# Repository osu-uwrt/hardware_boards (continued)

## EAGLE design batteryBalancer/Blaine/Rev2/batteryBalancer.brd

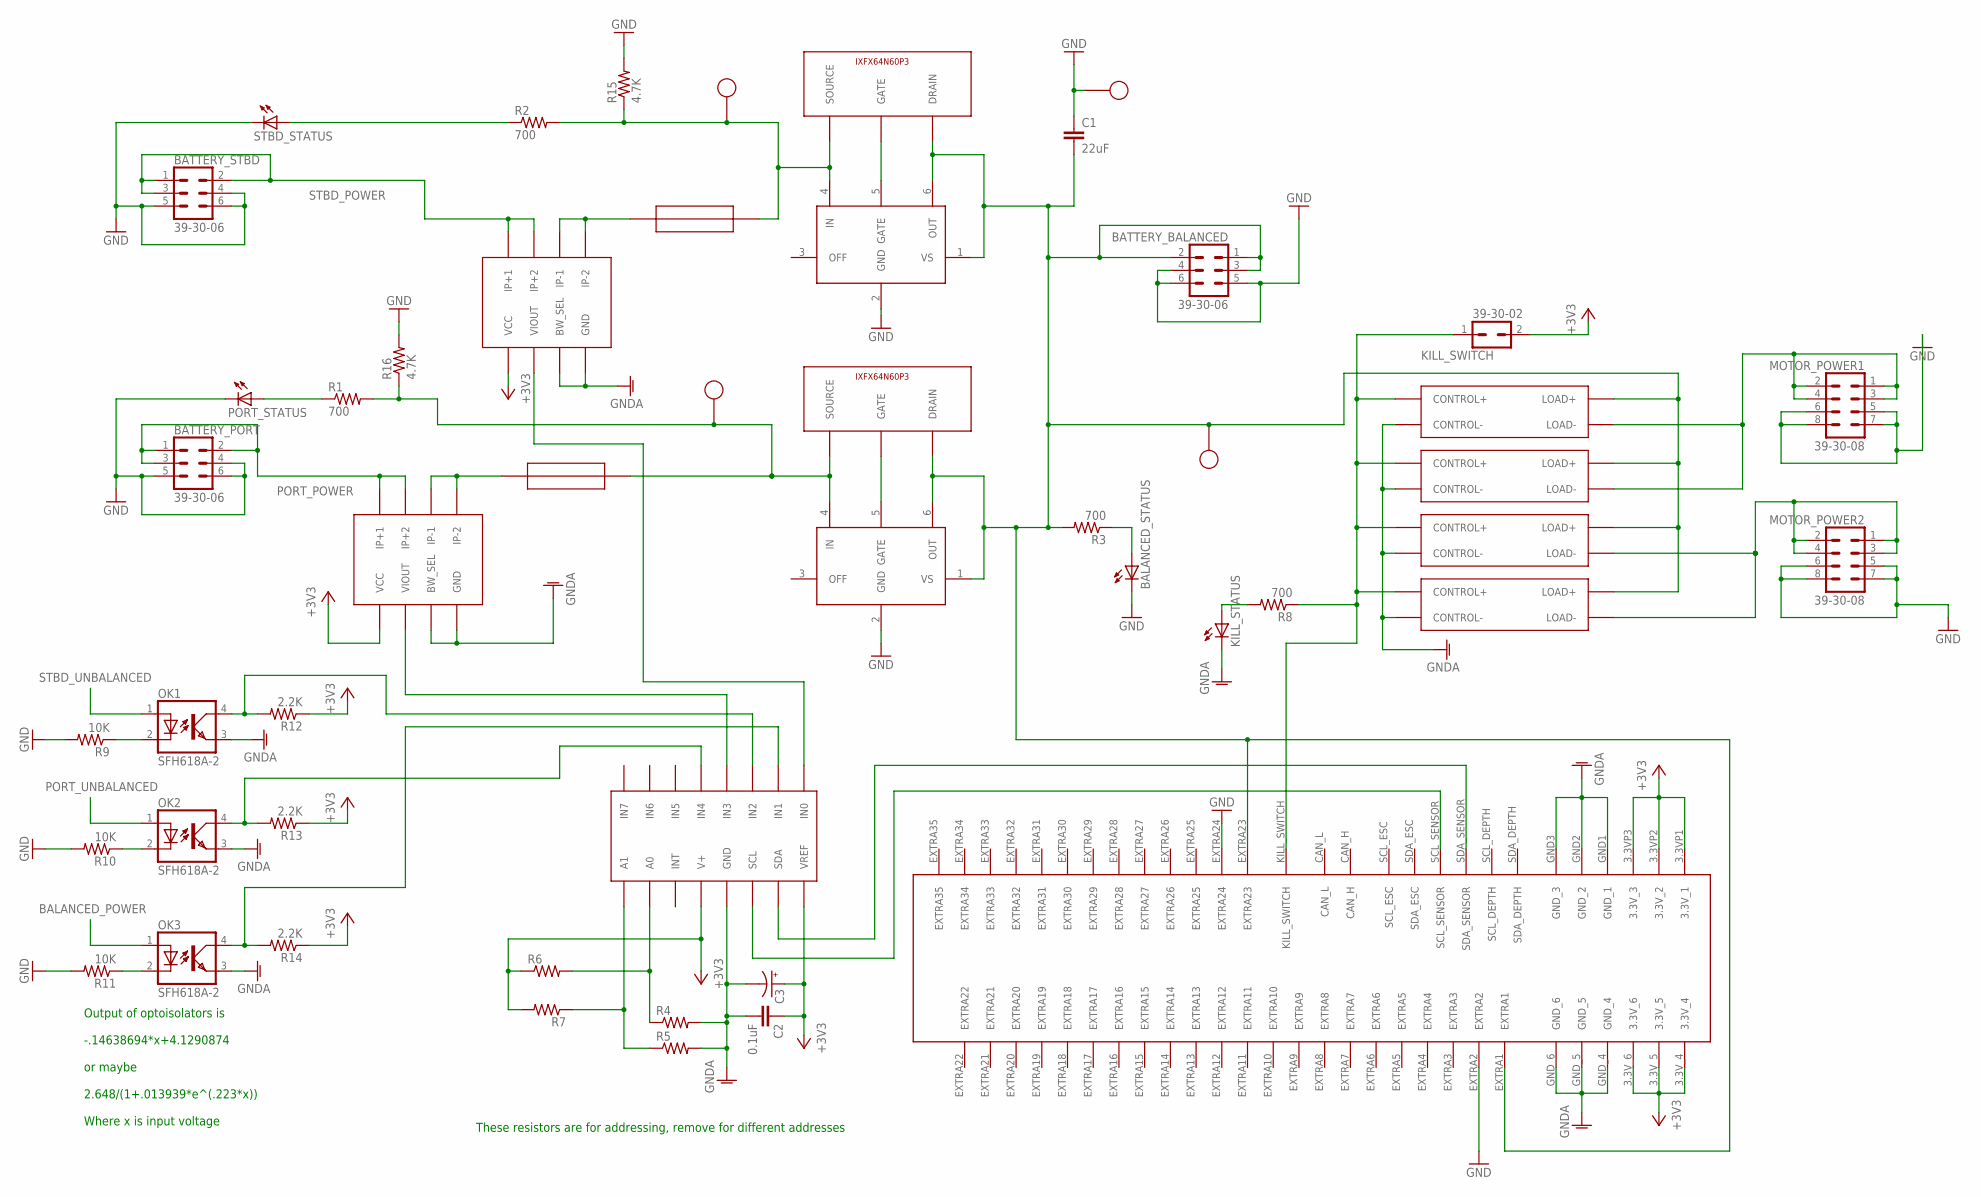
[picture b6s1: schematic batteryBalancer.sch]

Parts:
ADC: ADC128D818; TSSOP-16
BALANCED_STATUS: LTST-S270GKT
BATTERY_BALANCED: 39-30-06; 39-30-?06?
BATTERY_PORT: 39-30-06; 39-30-?06?
BATTERY_STBD: 39-30-06; 39-30-?06?
C1: 22uF; CAP-PTH-SMALL-KIT
C2: 0.1uF; CAP-PTH-SMALL-KIT
C3: CPOL-USE2-4; E2-4
EDGE_CONNECTOR: 5530843; 5530843-6-BOARDFINGERS
KILL_STATUS: LTST-S270GKT
KILL_SWITCH: 39-30-02; 39-30-?02?
MOTOR_POWER1, MOTOR_POWER2: 39-30-08; 39-30-?08?
OK1, OK2, OK3: SFH618A-2; DIP4
PORT_CS: ACS722; SOIC-8
PORT_FC: LM5050-1; SOT23-6
PORT_FET: IXFX64N60P3
PORT_FUSE: 01220083Z
PORT_STATUS: LTST-S270GKT
R1, R2, R3, R8: 700; 0207/7
R4, R5, R6, R7: R-US_0204/5; 0204/5
R9, R10, R11: 10K; 0207/7
R12, R13, R14: 2.2K; 0207/7
R15, R16: 4.7K; 0207/7
RELAY2, RELAY3, RELAY4: CMX60D20
RLAY1: CMX60D20
STBD_CS: ACS722; SOIC-8
STBD_FC: LM5050-1; SOT23-6
STBD_FET: IXFX64N60P3
STBD_FUSE: 01220083Z
STBD_STATUS: LTST-S270GKT
U$1, U$2, U$3, U$4: 5010_C

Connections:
3.3V: ADC.V+, ADC.VREF, C2.1, C3.+, EDGE_CONNECTOR.3.3VP1 (3.3V_1), EDGE_CONNECTOR.3.3VP2 (3.3V_2), EDGE_CONNECTOR.3.3VP3 (3.3V_3), EDGE_CONNECTOR.3.3V_4, EDGE_CONNECTOR.3.3V_5, EDGE_CONNECTOR.3.3V_6, KILL_SWITCH.2, PORT_CS.VCC, R6.1, R7.2, R12.1, R13.1, R14.1, STBD_CS.VCC
ADC_A0: ADC.A0, R4.1, R6.2
ADC_A1: ADC.A1, R5.1, R7.1
BALANCED_INDICATOR: BALANCED_STATUS.ANODE (A), R3.1
BALANCED_LOGIC: ADC.IN1, OK3.4 (COL), R14.2
BALANCED_OPTO_NEG: OK3.2 (C), R11.1
BALANCED_POWER: BATTERY_BALANCED.1, BATTERY_BALANCED.2, BATTERY_BALANCED.3, C1.2, EDGE_CONNECTOR.EXTRA1, EDGE_CONNECTOR.EXTRA23, OK3.1 (A), PORT_FC.1 (VS), PORT_FC.6 (OUT), PORT_FET.DRAIN, R3.2, RELAY2.LOAD+, RELAY3.LOAD+, RELAY4.LOAD+, RLAY1.LOAD+, STBD_FC.1 (VS), STBD_FC.6 (OUT), STBD_FET.DRAIN, U$3.P$1
GND: BALANCED_STATUS.CATHODE (C), BATTERY_BALANCED.4, BATTERY_BALANCED.5, BATTERY_BALANCED.6, BATTERY_PORT.4, BATTERY_PORT.5, BATTERY_PORT.6, BATTERY_STBD.4, BATTERY_STBD.5, BATTERY_STBD.6, C1.1, EDGE_CONNECTOR.EXTRA2, EDGE_CONNECTOR.EXTRA24, MOTOR_POWER1.5, MOTOR_POWER1.6, MOTOR_POWER1.7, MOTOR_POWER1.8, MOTOR_POWER2.5, MOTOR_POWER2.6, MOTOR_POWER2.7, MOTOR_POWER2.8, PORT_FC.2 (GND), PORT_STATUS.CATHODE (C), R9.2, R10.2, R11.2, R15.2, R16.2, STBD_FC.2 (GND), STBD_STATUS.CATHODE (C), U$4.P$1
KILL_SWITCH: EDGE_CONNECTOR.KILL_SWITCH, KILL_SWITCH.1, R8.1, RELAY2.CONTROL+, RELAY3.CONTROL+, RELAY4.CONTROL+, RLAY1.CONTROL+
LOGIC_GND: ADC.GND, C2.2, C3.-, EDGE_CONNECTOR.GND1 (GND_1), EDGE_CONNECTOR.GND2 (GND_2), EDGE_CONNECTOR.GND3 (GND_3), EDGE_CONNECTOR.GND_4, EDGE_CONNECTOR.GND_5, EDGE_CONNECTOR.GND_6, KILL_STATUS.CATHODE (C), OK1.3 (EMIT), OK2.3 (EMIT), OK3.3 (EMIT), PORT_CS.BW_SEL, PORT_CS.GND, R4.2, R5.2, RELAY2.CONTROL-, RELAY3.CONTROL-, RELAY4.CONTROL-, RLAY1.CONTROL-, STBD_CS.BW_SEL, STBD_CS.GND
MOTOR_POWER1: MOTOR_POWER1.1, MOTOR_POWER1.2, MOTOR_POWER1.3, MOTOR_POWER1.4, RELAY2.LOAD-, RLAY1.LOAD-
MOTOR_POWER2: MOTOR_POWER2.1, MOTOR_POWER2.2, MOTOR_POWER2.3, MOTOR_POWER2.4, RELAY3.LOAD-, RELAY4.LOAD-
unnamed: KILL_STATUS.ANODE (A), R8.2
PORT_CURRENT: ADC.IN3, PORT_CS.VIOUT
PORT_GATE: PORT_FC.5 (GATE), PORT_FET.GATE
PORT_LOGIC: ADC.IN4, OK2.4 (COL), R13.2
PORT_OPTO_NEG: OK2.2 (C), R10.1
PORT_POWER: BATTERY_PORT.1, BATTERY_PORT.2, BATTERY_PORT.3, PORT_CS.IP+1, PORT_CS.IP+2
PORT_STATUS: PORT_STATUS.ANODE (A), R1.1
PORT_UNBALANCED: OK2.1 (A), PORT_FC.4 (IN), PORT_FET.SOURCE, PORT_FUSE.P$3, PORT_FUSE.P$4, R1.2, R16.1, U$2.P$1
PORT_UNFUSED: PORT_CS.IP-1, PORT_CS.IP-2, PORT_FUSE.P$1, PORT_FUSE.P$2
SCL: ADC.SCL, EDGE_CONNECTOR.SCL_SENSOR
SDA: ADC.SDA, EDGE_CONNECTOR.SDA_SENSOR
STBD_CURRENT: ADC.IN0, STBD_CS.VIOUT
STBD_GATE: STBD_FC.5 (GATE), STBD_FET.GATE
STBD_LOGIC: ADC.IN2, OK1.4 (COL), R12.2
STBD_OPTO_NEG: OK1.2 (C), R9.1
STBD_POWER: BATTERY_STBD.1, BATTERY_STBD.2, BATTERY_STBD.3, STBD_CS.IP+1, STBD_CS.IP+2
STBD_STATUS: R2.1, STBD_STATUS.ANODE (A)
STBD_UNBALANCED: OK1.1 (A), R2.2, R15.1, STBD_FC.4 (IN), STBD_FET.SOURCE, STBD_FUSE.P$3, STBD_FUSE.P$4, U$1.P$1
STBD_UNFUSED: STBD_CS.IP-1, STBD_CS.IP-2, STBD_FUSE.P$1, STBD_FUSE.P$2

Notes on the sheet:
These resistors are for addressing, remove for different addresses
Output of optoisolators is -.14638694*x+4.1290874 or maybe 2.648/(1+.013939*e^(.223*x)) Where x is input voltage

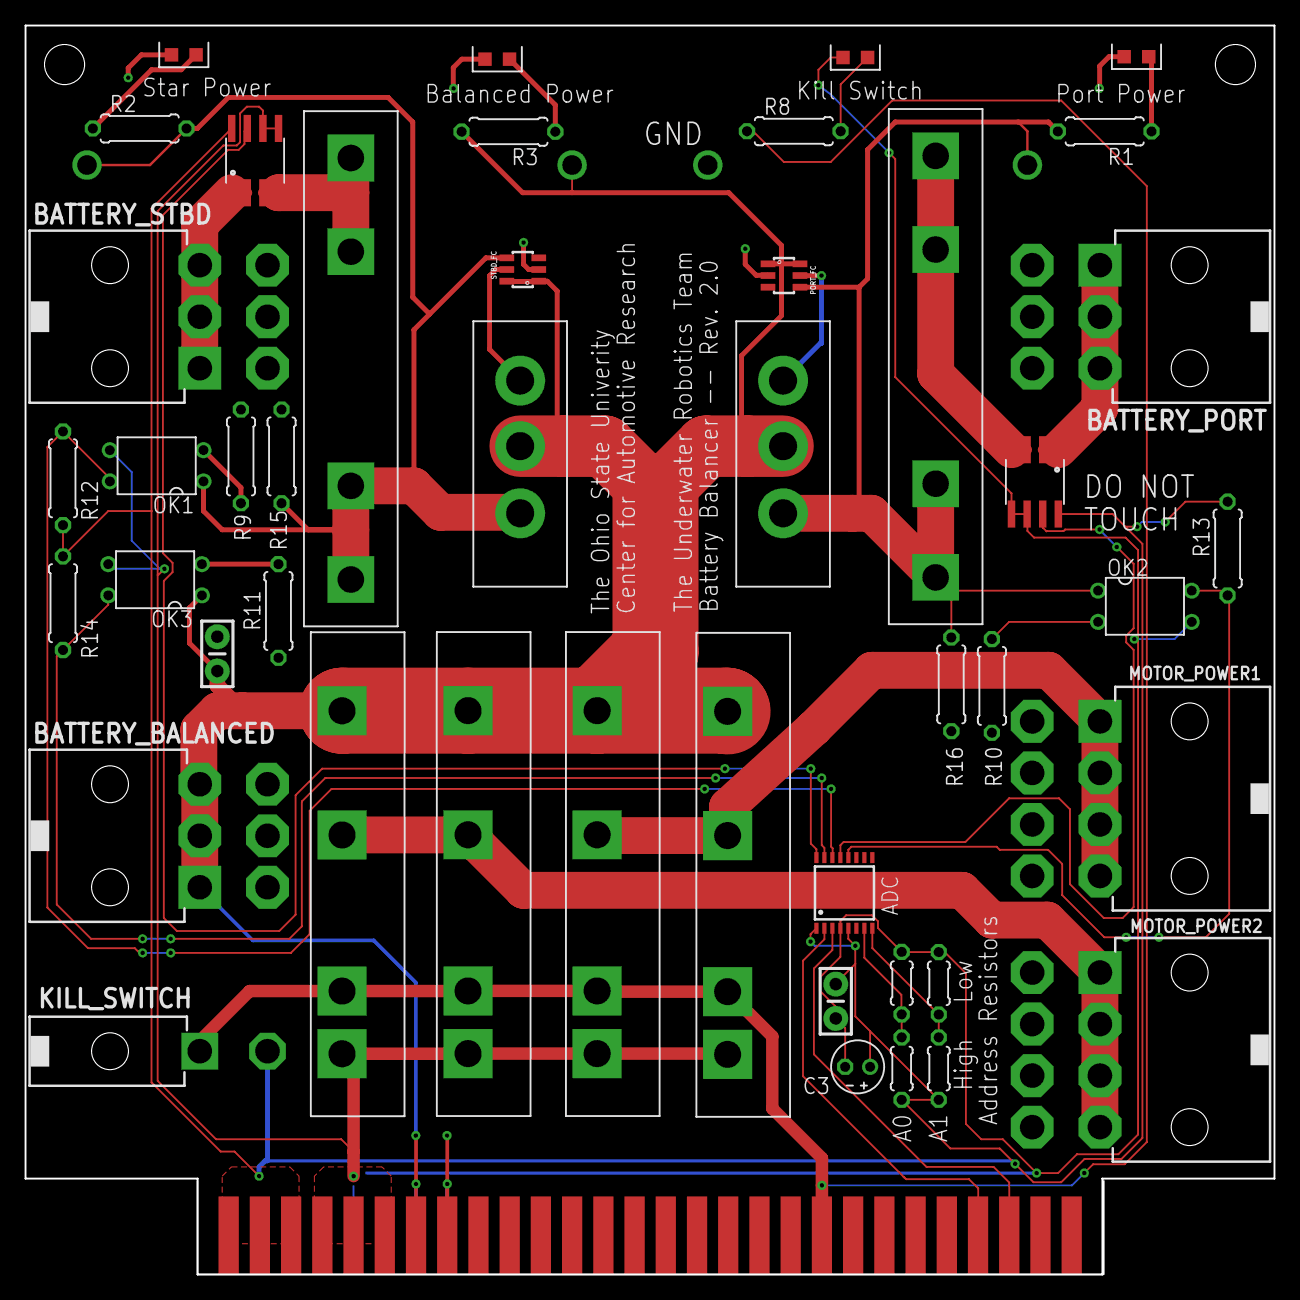
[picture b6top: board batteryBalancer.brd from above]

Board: 2 copper layers, 101.6 x 101.6 mm, 50 parts (0 on the bottom side), 31 nets.

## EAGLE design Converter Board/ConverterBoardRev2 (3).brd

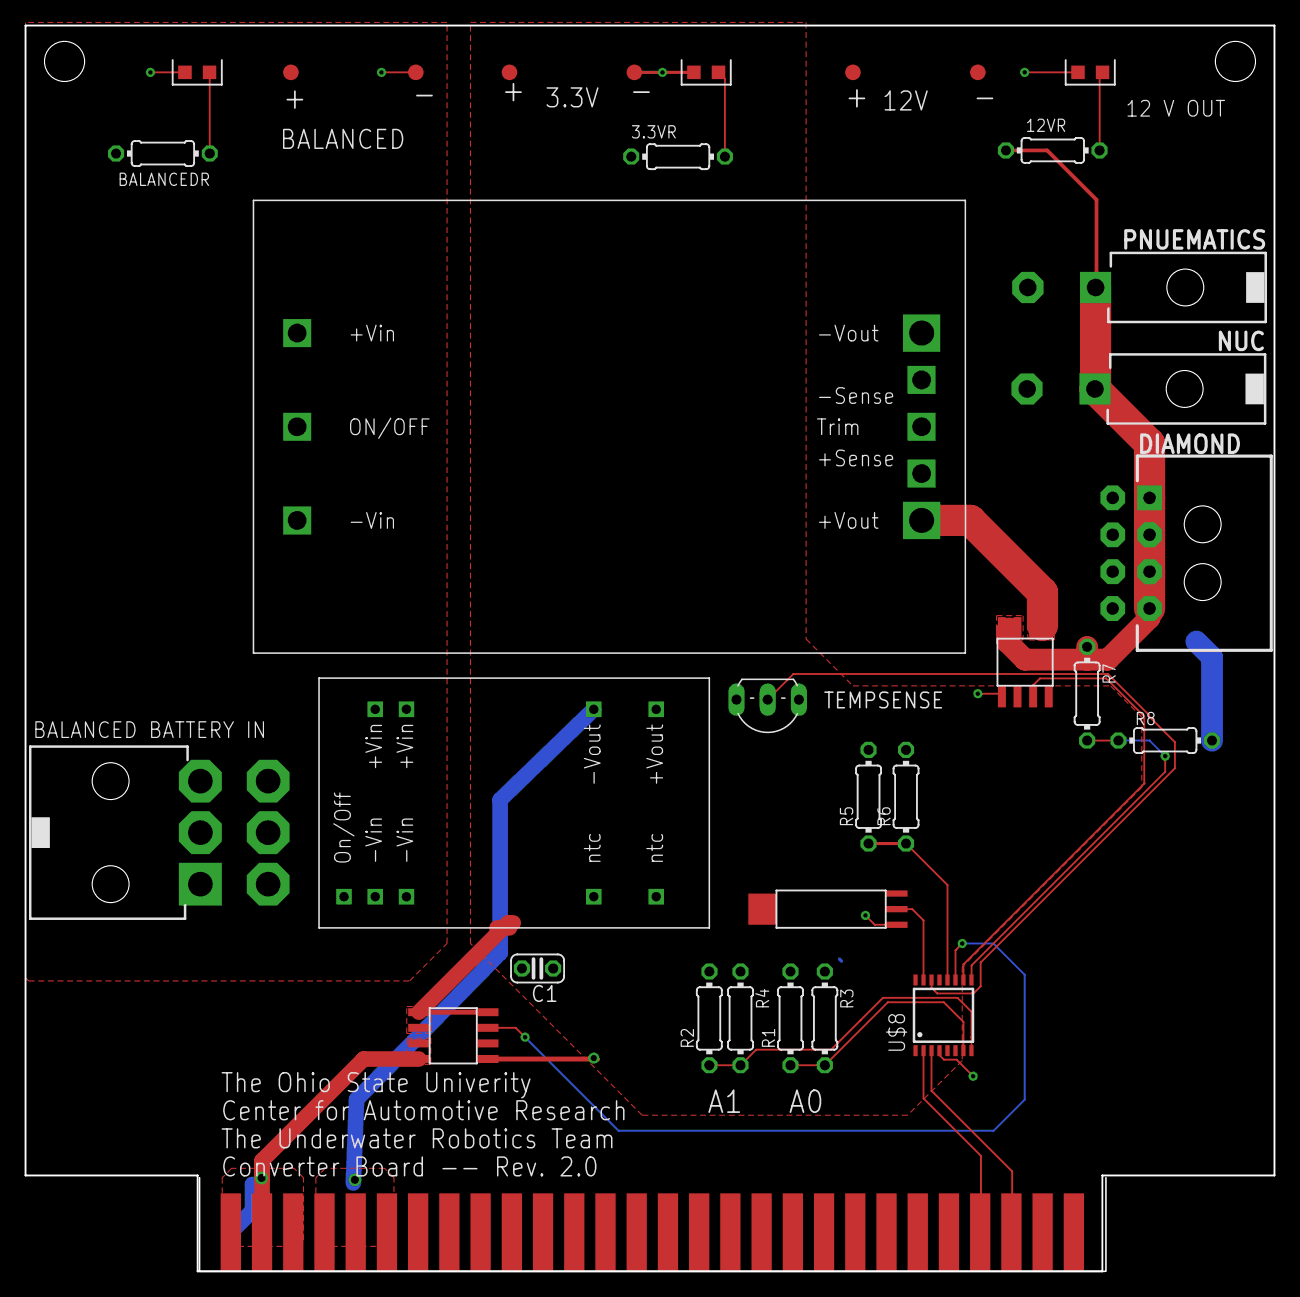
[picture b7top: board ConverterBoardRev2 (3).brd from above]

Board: 2 copper layers, 101.6 x 101.3 mm, 33 parts (0 on the bottom side), 21 nets.

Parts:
3.3V+TP, 3.3V-TP, 12V+TP, 12V-TP: PTR1B1,27; B1,27
3.3VLED, 12VLED: LTST-S270GKT
3.3VR, 12VR: 330; 0204/7
3V3CUR, 12VCUR: CURRENTSENS
BALANCED+TP: PTR1B1,27; B1,27
BALANCED-TP: PTR1B1,27; B1,27
BALANCEDLED: LTST-S270GKT
BALANCEDR: 700; 0204/7
BALANCEDRAWIN: 39-30-06?; 39-30-?06?
C1: 0.1 uF; C025-024X044
DIAMOND: 43045-08
NUC: 39-30-02?; 39-30-?02?
PNUEMATICS: 39-30-02?; 39-30-?02?
R1, R2, R3, R4, R5, R6, R7, R8: 0204/7
TEMPSENSE: 2SC458; TO92-ECB
U$1: 12VCONV
U$2: 3.3VCONV
U$3: 5530843; 5530843-6-BOARDFINGERS
U$6: HUMIDITYSENSOR
U$8: ADC128D818; TSSOP-16

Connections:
3.3IDATA: 3V3CUR.7,VIOUT, U$8.IN5
3.3V+: 3.3V+TP.TP, 3.3VR.2, 3V3CUR.1,IP+, 3V3CUR.2,IP+, 3V3CUR.8,VCC, 12VCUR.8,VCC, C1.2, R1.2, R2.2, R6.2, TEMPSENSE.E, U$2.14, U$6.+VE, U$8.V+, U$8.VREF
3.3V-: 3.3V-TP.TP, 3.3VLED.CATHODE, 3V3CUR.5,GND, 12VCUR.5,GND, C1.1, R3.1, R4.1, R5.2, TEMPSENSE.B, U$2.16, U$3.GND1, U$3.GND2, U$3.GND3, U$3.GND_4, U$3.GND_5, U$3.GND_6, U$6.-VE, U$8.GND
3.3VBKPLN: 3V3CUR.3,IP-, 3V3CUR.4,IP-, U$3.3.3VP1, U$3.3.3VP2, U$3.3.3VP3, U$3.3.3V_4, U$3.3.3V_5, U$3.3.3V_6
3.3VDATA: R5.1, R6.1, U$8.IN4
3.3VLED: 3.3VLED.ANODE, 3.3VR.1
12IDATA: 12VCUR.7,VIOUT, U$8.IN6
12VDATA: R7.2, R8.1, U$8.IN7
12VGND: 12V-TP.TP, 12VLED.CATHODE, DIAMOND.5, DIAMOND.6, DIAMOND.7, DIAMOND.8, NUC.2, PNUEMATICS.2, R8.2, U$1.4,-VOUT
12VLED: 12VLED.ANODE, 12VR.2
12VMON: 12VCUR.3,IP-, 12VCUR.4,IP-, 12VR.1, DIAMOND.1, DIAMOND.2, DIAMOND.3, DIAMOND.4, NUC.1, PNUEMATICS.1, R7.1
12VUNMON: 12VCUR.1,IP+, 12VCUR.2,IP+, U$1.8,+VOUT
A0: R1.1, R3.2, U$8.A0
A1: R2.1, R4.2, U$8.A1
BALANCED+: BALANCED+TP.TP, BALANCEDR.2, BALANCEDRAWIN.4, BALANCEDRAWIN.5, BALANCEDRAWIN.6, U$1.1,+VIN, U$1.2,ON/OFF, U$2.22, U$2.23
BALANCED-: BALANCED-TP.TP, BALANCEDLED.CATHODE, BALANCEDRAWIN.1, BALANCEDRAWIN.2, BALANCEDRAWIN.3, U$1.3,-VIN, U$2.1, U$2.2, U$2.3
BALANCEDLED: BALANCEDLED.ANODE, BALANCEDR.1
HUMIDITYDATA: U$6.OUT, U$8.IN1
SCL: U$3.SCL_SENSOR, U$8.SCL
SDA: U$3.SDA_SENSOR, U$8.SDA
TEMPDATA: TEMPSENSE.C, U$8.IN2

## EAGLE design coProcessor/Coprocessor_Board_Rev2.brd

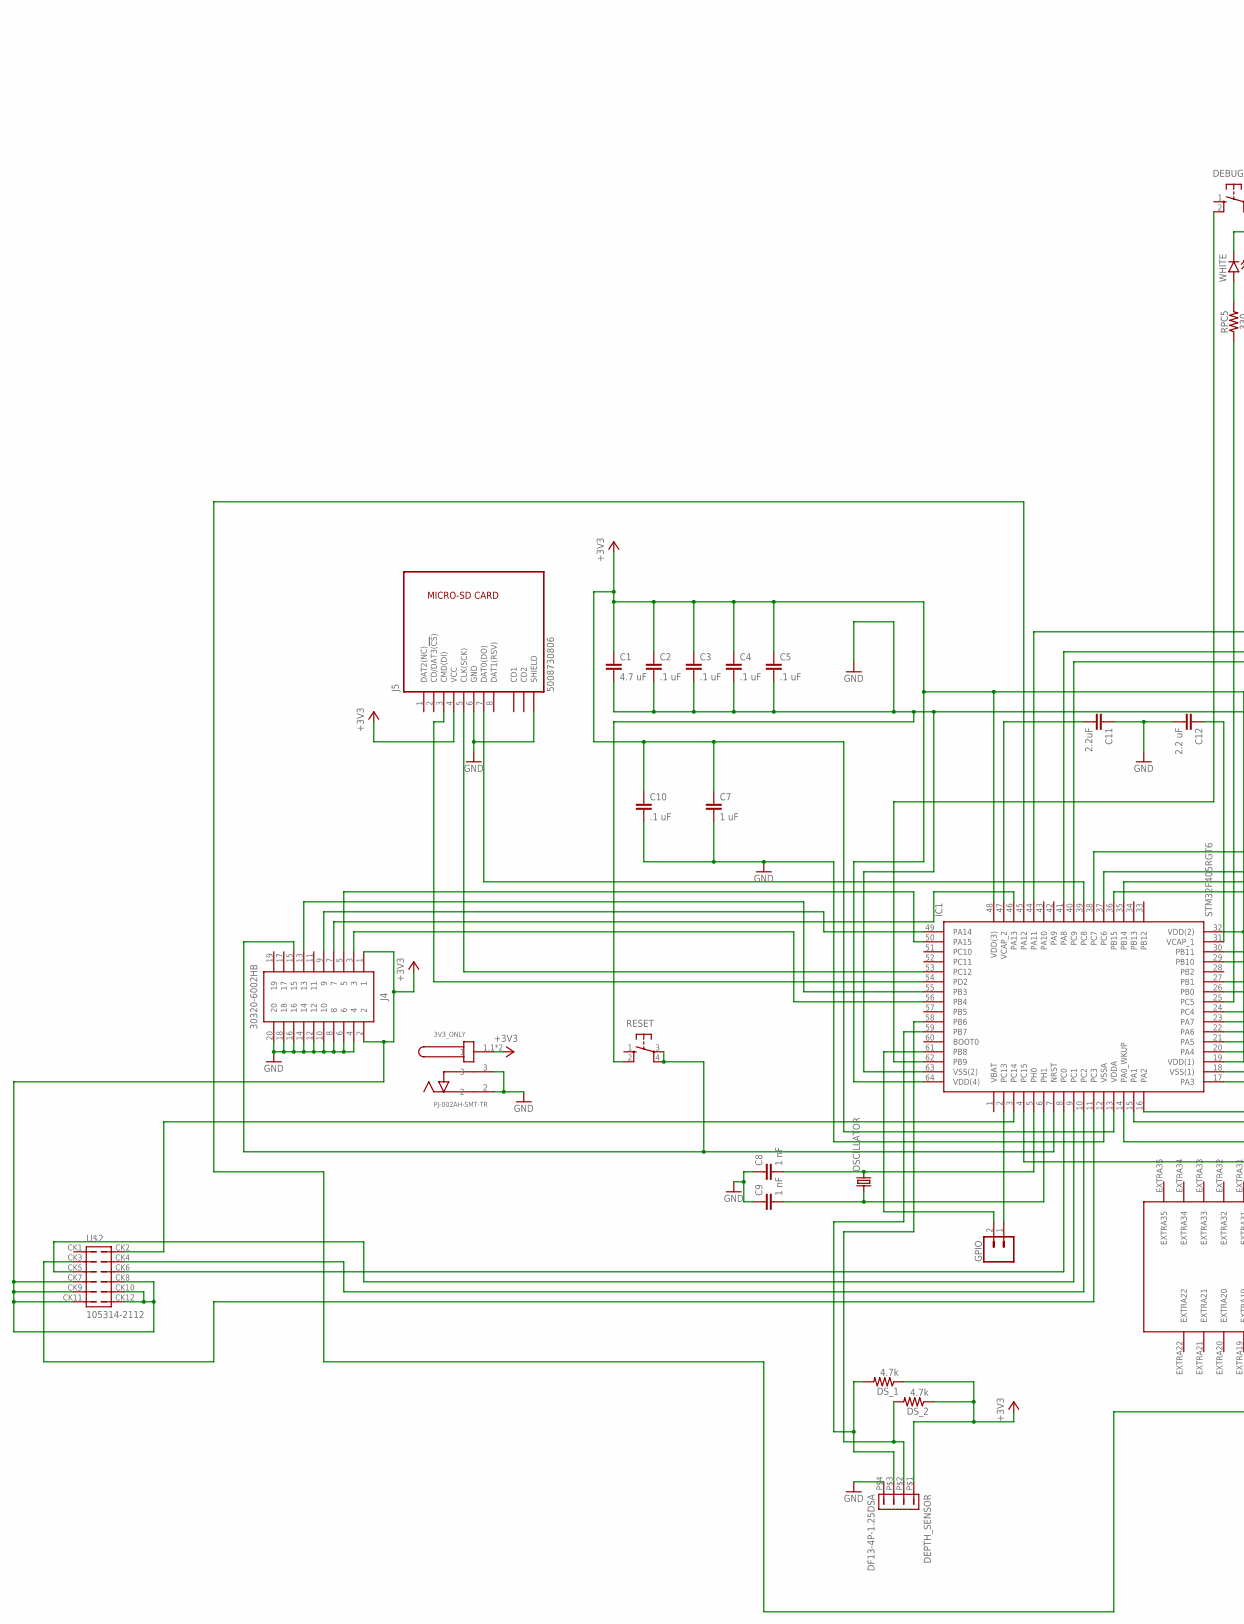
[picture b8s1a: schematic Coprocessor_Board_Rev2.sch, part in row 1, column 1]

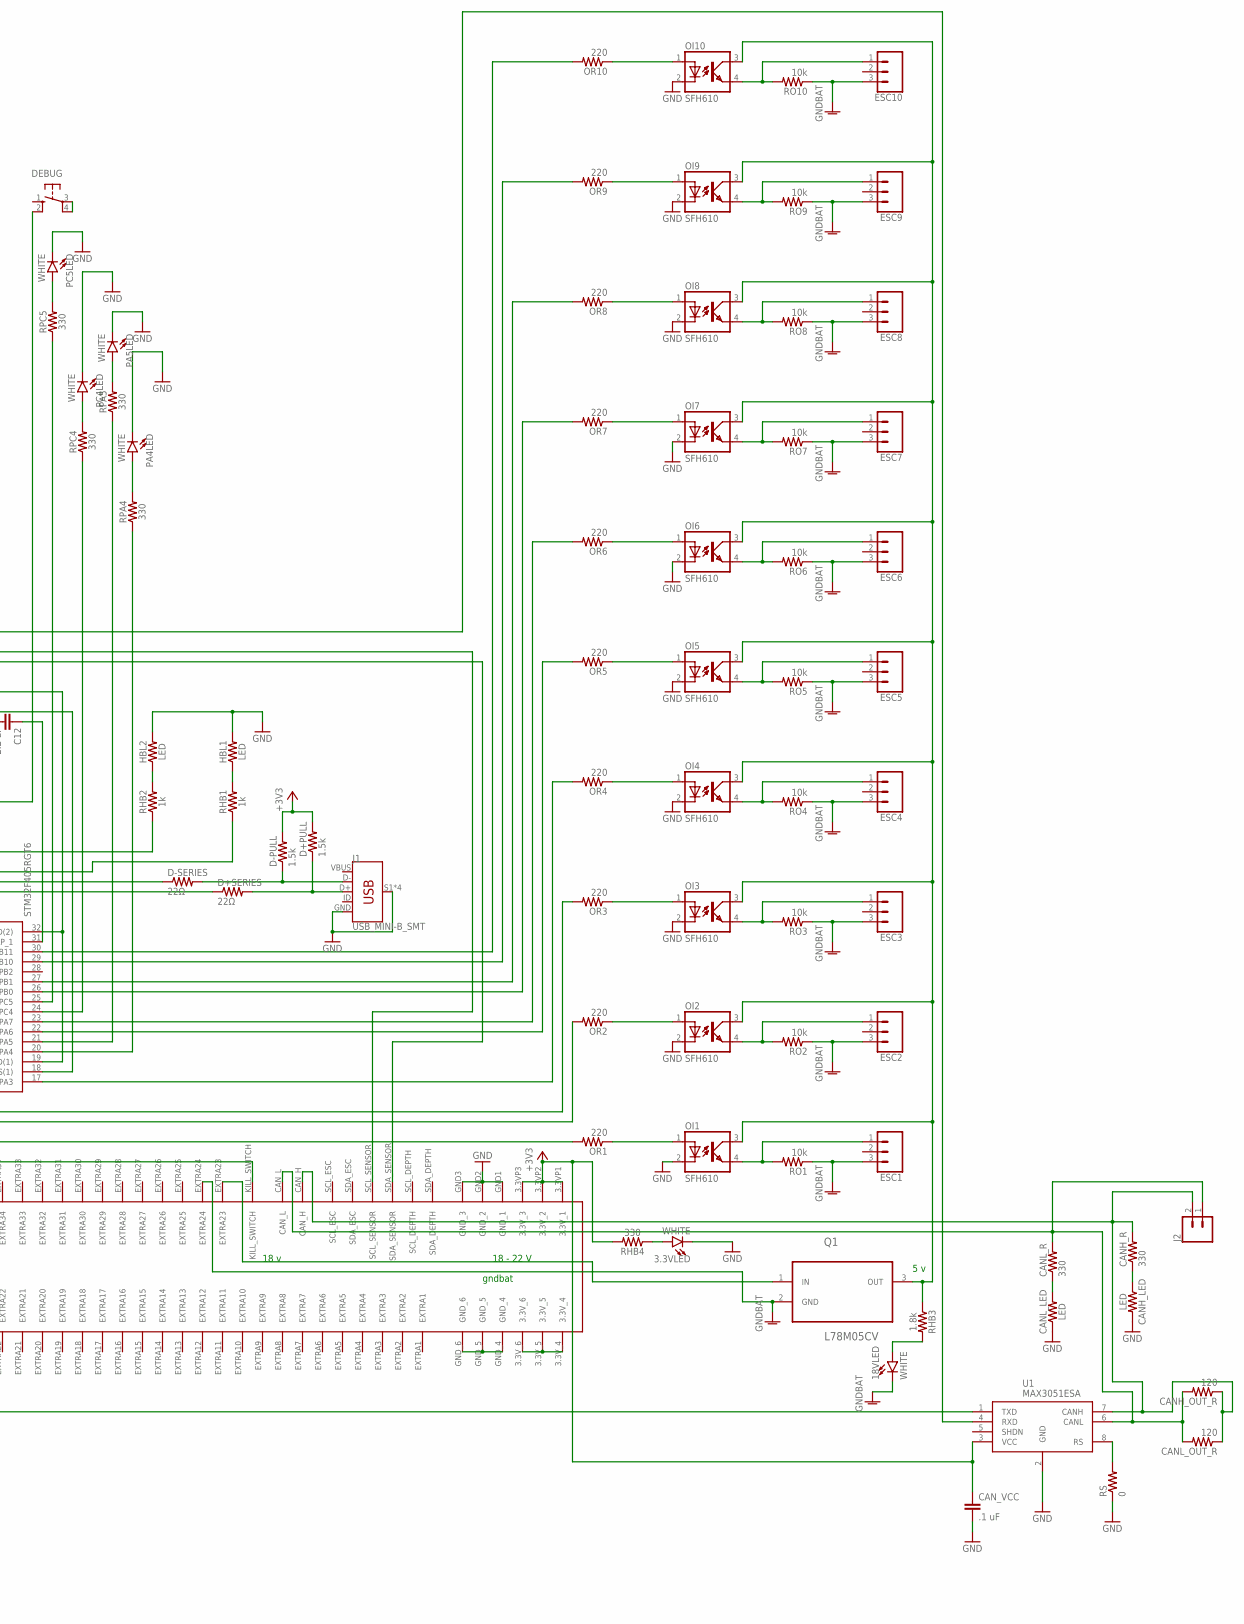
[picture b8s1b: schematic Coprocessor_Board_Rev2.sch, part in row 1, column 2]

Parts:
3.3VLED, 18VLED: WHITE; LED-1206
3V3_ONLY: PJ-002AH-SMT-TR; CUI_PJ-002AH-SMT-TR
C1: 4.7 uF; 0603
C2, C3, C4, C5, C10: .1 uF; 0603
C7: 1 uF; 0603
C8, C9: 1 nF; CAP-PTH-2.54
C11: 2.2uF; 0603
C12: 2.2 uF; 0603
CANH_LED: LED; AXIAL-0.1
CANH_OUT_R: 120; 0204/7
CANH_R: 330; 0204/7
CANL_LED: LED; AXIAL-0.1
CANL_OUT_R: 120; 0204/7
CANL_R: 330; 0204/7
CAN_VCC: .1 uF; CAP-PTH-2.54
D+PULL: 1.5k; 0204/7
D+SERIES: 22Ω; 0204/7
D-PULL: 1.5k; 0204/7
D-SERIES: 22Ω; 0204/7
DEBUG: 10-XX; B3F-10XX
DEPTH_SENSOR: DF13-4P-1.25DSA
DS_1, DS_2: 4.7k; 0204/7
ESC1, ESC2, ESC3, ESC4, ESC5, ESC6, ESC7, ESC8, ESC9, ESC10: CONN_03; 1X03
GPIO: CONN_02; 1X02
HBL1, HBL2: LED; AXIAL-0.1
IC1: STM32F405RGT6; QFP50P1200X1200X160-64N
J1: USB_MINI-B_SMT; USB-MINIB
J2: CONN_02; 1X02
J4: 30320-6002HB; SHDR20W81P254_2X10_3300X840X93
J5: 5008730806
OI1, OI2, OI3, OI4, OI5, OI6, OI7, OI8, OI9, OI10: SFH610; DIL04
OR1, OR2, OR3, OR4, OR5, OR6, OR7, OR8, OR9, OR10: 220; 0204/7
OSCILLATOR: CRYSTALHC49S; HC49/S
PA4LED, PA5LED: WHITE; LED-1206
PC4LED, PC5LED: WHITE; LED-1206
Q1: L78M05CV; TO254P450X1020X1935-3P
RESET: 10-XX; B3F-10XX
RHB1, RHB2: 1k; AXIAL-0.3
RHB3: 1.8k; AXIAL-0.3
RHB4: 330; AXIAL-0.3
RO1, RO2, RO3, RO4, RO5, RO6, RO7, RO8, RO9, RO10: 10k; 0204/7
RPA4, RPA5: 330; AXIAL-0.3
RPC4, RPC5: 330; AXIAL-0.3
RS: 0; 0204/7
U1: MAX3051ESA; 8-SOICN
U$1: 5530843; 5530843-6-BOARDFINGERS
U$2: 105314-2112

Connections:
3.3V: 3V3_ONLY.1.1 (1), 3V3_ONLY.1.2 (1), C1.1, C2.1, C3.1, C4.1, C5.1, C7.1, C10.1, CAN_VCC.1, D+PULL.2, D-PULL.2, DEPTH_SENSOR.P$1 (1), DS_1.1, DS_2.1, IC1.13 (VDDA), IC1.19 (VDD(1)), IC1.32 (VDD(2)), IC1.48 (VDD(3)), IC1.64 (VDD(4)), J4.1, J4.2, J5.4 (VCC), RHB4.P$2 (2), U1.3 (VCC), U$1.3.3VP1 (3.3V_1), U$1.3.3VP2 (3.3V_2), U$1.3.3VP3 (3.3V_3), U$1.3.3V_4, U$1.3.3V_5, U$1.3.3V_6, U$2.CK7, U$2.CK8, U$2.CK9, U$2.CK10, U$2.CK11, U$2.CK12
5V: OI1.3 (COL), OI2.3 (COL), OI3.3 (COL), OI4.3 (COL), OI5.3 (COL), OI6.3 (COL), OI7.3 (COL), OI8.3 (COL), OI9.3 (COL), OI10.3 (COL), Q1.3 (OUT), RHB3.P$1 (1)
18V: Q1.1 (IN), U$1.EXTRA23
CAN1_RXD: IC1.44 (PA11), U1.4 (RXD)
CAN1_TXD: IC1.45 (PA12), U1.1 (TXD)
CANH: CANH_OUT_R.1, CANH_R.2, CANL_OUT_R.1, J2.2, U1.7 (CANH), U$1.CAN_H
CANL: CANH_OUT_R.2, CANL_OUT_R.2, CANL_R.2, J2.1, U1.6 (CANL), U$1.CAN_L
D+CON: D+PULL.1, D+SERIES.2, J1.D+
D-CON: D-PULL.1, D-SERIES.2, J1.D-
DEPTHSCL: DEPTH_SENSOR.P$2 (2), DS_2.2, IC1.58 (PB6)
DEPTHSDA: DEPTH_SENSOR.P$3 (3), DS_1.2, IC1.59 (PB7)
GNDBAT: 18VLED.C, ESC1.3, ESC2.3, ESC3.3, ESC4.3, ESC5.3, ESC6.3, ESC7.3, ESC8.3, ESC9.3, ESC10.3, Q1.2 (GND), RO1.1, RO2.1, RO3.1, RO4.1, RO5.1, RO6.1, RO7.1, RO8.1, RO9.1, RO10.1, U$1.EXTRA24
HEARTBEAT_1: IC1.37 (PC6), RHB1.P$1 (1)
HEARTBEAT_2: IC1.38 (PC7), RHB2.P$1 (1)
HEARTBEAT_3: IC1.20 (PA4), RPA4.P$1 (1)
HEARTBEAT_4: IC1.21 (PA5), RPA5.P$1 (1)
HEAVE_PORT_AFT: IC1.27 (PB1), OR8.2
HEAVE_PORT_FWD: IC1.26 (PB0), OR7.2
HEAVE_STBD_AFT: IC1.23 (PA7), OR6.2
HEAVE_STBD_FWD: IC1.22 (PA6), OR5.2
JTAG15: IC1.7 (NRST), J4.15, RESET.3, RESET.4 (P1)
KILLSWITCH: IC1.4 (PC15), U$1.KILL_SWITCH
MISSION_START: IC1.8 (PC0), U$2.CK6
unnamed: HBL1.P$1 (1), RHB1.P$2 (2)
unnamed: RS.2, U1.8 (RS)
unnamed: 18VLED.A, RHB3.P$2 (2)
unnamed: 3.3VLED.A, RHB4.P$1 (1)
unnamed: CANH_LED.P$1 (1), CANH_R.1
unnamed: CANL_LED.P$2 (2), CANL_R.1
unnamed: PA4LED.A, RPA4.P$2 (2)
unnamed: PA5LED.A, RPA5.P$2 (2)
unnamed: PC4LED.A, RPC4.P$2 (2)
unnamed: PC5LED.A, RPC5.P$2 (2)
unnamed: HBL2.P$1 (1), RHB2.P$2 (2)
PB8: GPIO.2, IC1.61 (PB8)
PB9: DEBUG.2 (S1), IC1.62 (PB9)
PC4: IC1.24 (PC4), RPC4.P$1 (1)
PC5: IC1.25 (PC5), RPC5.P$1 (1)
PC13: GPIO.1, IC1.2 (PC13)
PWM1: OI1.1 (A), OR1.1
PWM2: OI2.1 (A), OR2.1
PWM3: OI3.1 (A), OR3.1
PWM4: OI4.1 (A), OR4.1
PWM5: OI5.1 (A), OR5.1
PWM5V1: ESC1.1, OI1.4 (EMIT), RO1.2
PWM5V2: ESC2.1, OI2.4 (EMIT), RO2.2
PWM5V3: ESC3.1, OI3.4 (EMIT), RO3.2
PWM5V4: ESC4.1, OI4.4 (EMIT), RO4.2
PWM5V5: ESC5.1, OI5.4 (EMIT), RO5.2
PWM5V6: ESC6.1, OI6.4 (EMIT), RO6.2
PWM5V7: ESC7.1, OI7.4 (EMIT), RO7.2
PWM5V8: ESC8.1, OI8.4 (EMIT), RO8.2
PWM5V9: ESC9.1, OI9.4 (EMIT), RO9.2
PWM5V10: ESC10.1, OI10.4 (EMIT), RO10.2
PWM6: OI6.1 (A), OR6.1
PWM7: OI7.1 (A), OR7.1
PWM8: OI8.1 (A), OR8.1
PWM9: OI9.1 (A), OR9.1
PWM10: OI10.1 (A), OR10.1
RCC_OSC_IN: C8.2, IC1.5 (PH0), OSCILLATOR.2
RCC_OSC_OUT: C9.2, IC1.6 (PH1), OSCILLATOR.1
SCL_BKPLN: IC1.41 (PA8), U$1.SCL_SENSOR
SDA_BKPLN: IC1.40 (PC9), U$1.SDA_SENSOR
SDIO_CK: IC1.53 (PC12), J5.5 (CLK(SCK))
SDIO_CMD: IC1.54 (PD2), J5.3 (CMD(DI))
SDIO_DO: IC1.39 (PC8), J5.7 (DAT0(DO))
SURGEPORTHI: IC1.16 (PA2), OR3.2
SURGEPORTLOW: IC1.17 (PA3), OR4.2
SURGESTBDHI: IC1.14 (PA0_WKUP), OR1.2
SURGESTBDLOW: IC1.15 (PA1), OR2.2
SWITCH6: IC1.3 (PC14), U$2.CK2
SWITCH_3: IC1.9 (PC1), U$2.CK5
SWITCH_4: IC1.10 (PC2), U$2.CK4
SWITCH_5: IC1.11 (PC3), U$2.CK3
SW_AFT: IC1.29 (PB10), OR9.2
SW_FWD: IC1.30 (PB11), OR10.2
SYS_JTCK-SWCLK: IC1.49 (PA14), J4.9
SYS_JTDI: IC1.46 (PA13), J4.7
SYS_JTDO-SWO: IC1.55 (PB3), J4.13
SYS_JTMS-SWIDIO: IC1.50 (PA15), J4.5
SYS_JTRST: IC1.56 (PB4), J4.3
USB_OTG_HS_DM: D-SERIES.1, IC1.35 (PB14)
USB_OTG_HS_DP: D+SERIES.1, IC1.36 (PB15)
VBUS: J1.VBUS
VCAP: C11.2, IC1.47 (VCAP_2)
VCAP2: C12.1, IC1.31 (VCAP_1)

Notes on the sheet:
5 v
18 - 22 V
18 v
gndbat

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
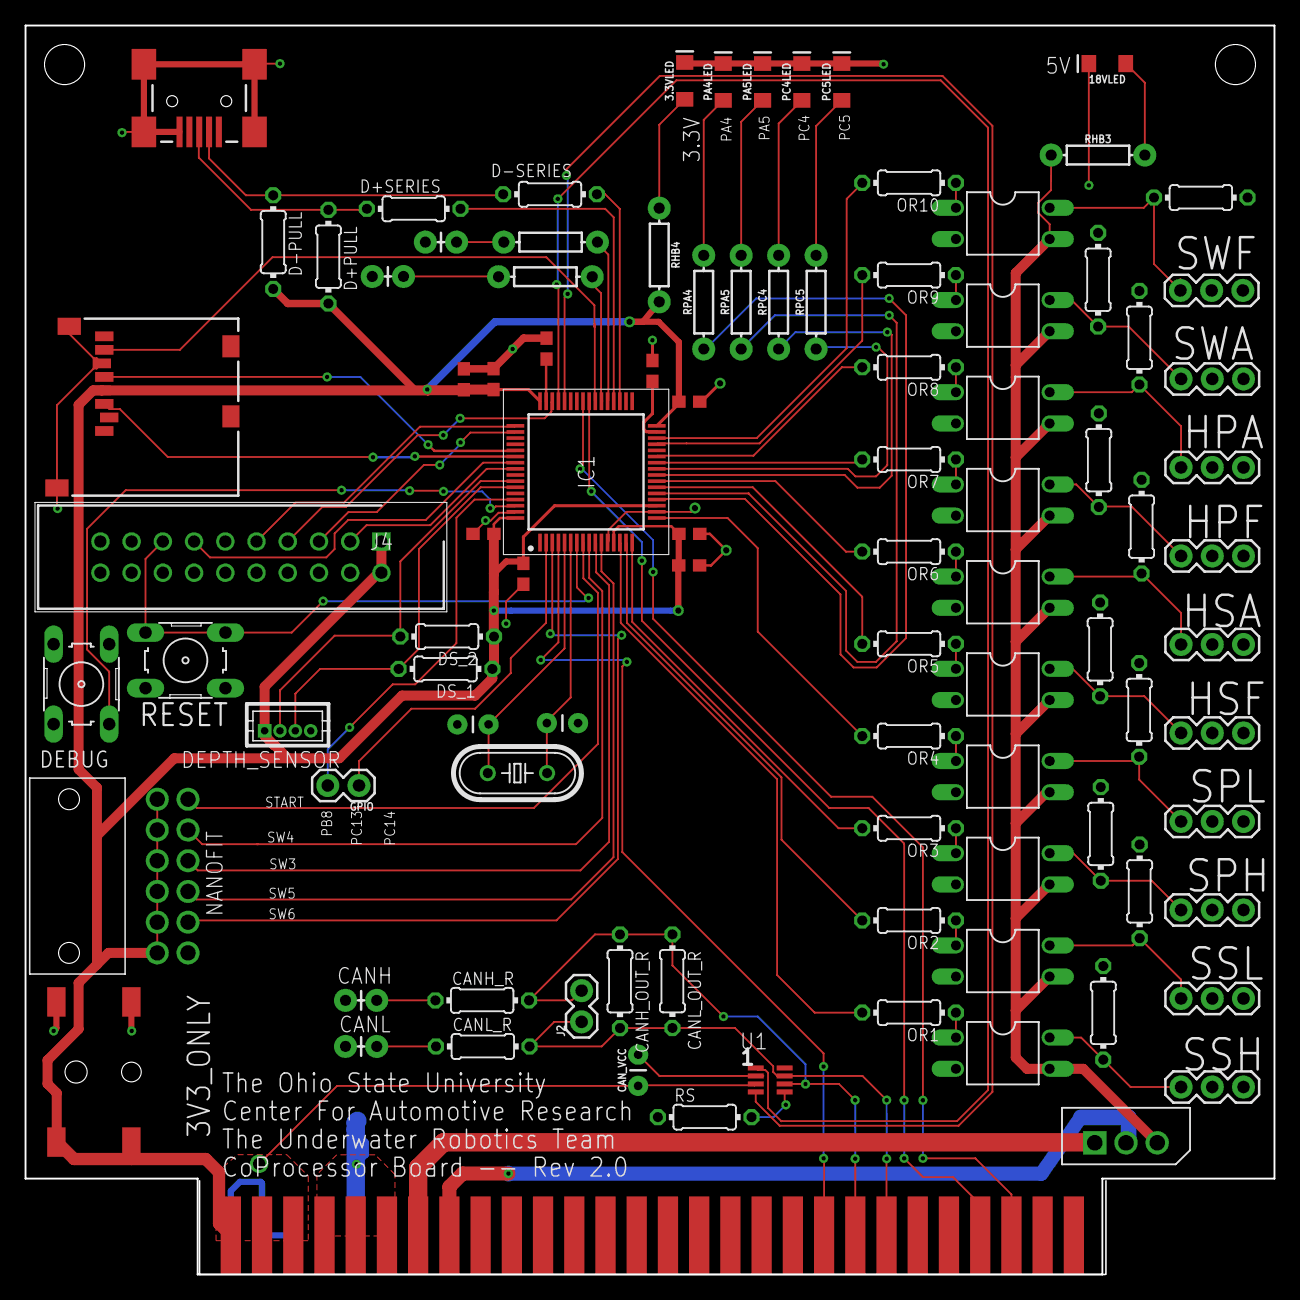
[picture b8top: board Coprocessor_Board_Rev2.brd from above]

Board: 2 copper layers, 101.6 x 101.6 mm, 96 parts (0 on the bottom side), 86 nets.

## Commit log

2017-08-23 Created README
2017-08-23 Initial commit of riptide boards
2017-08-27 Leo Sato Editing
2017-08-28 First commit of the batteryBalancer with the board temp
2017-08-28 Added my name to the ReadMe
2017-08-28 Rev1 Board
2017-08-30 Adding initial board template to repo
2017-08-31 Battery load balencer board rev 1.1 to be printed
2017-08-31 Gerber Files for Battery Balancer
2017-08-31 Edgefinger not connected
2017-09-06 Leaving the old boards (reluctantly) in the repo
2017-09-25 Modified ds store
2017-09-25 Adding blank folder for eagle libs and parts
2017-09-25 Adding the bulk of all Eagle Libs from the internet that are used
2017-10-02 Edge Connector parts revision 1 (10/1/17)
2017-10-05 Cleaning up september boards for noobs
2017-10-05 Initial commit of the battery balancer board
2017-10-05 Backplane V1, new edge layout for 2017
2017-10-07 Finished V1
2017-10-08 Updated backplane with all topside traces, correct planes.
2017-10-08 Re-do with dimensions agreeing with mechanical team
2017-10-08 Added 5 V converter part
2017-10-08 Fixed some parts and named parts
2017-10-08 Added the 3.3 Volt converter
2017-10-08 Revised the 3.3 converter
2017-10-08 Fancied up the schematic, nets still need to be named
2017-10-09 Fixed some connection errors
2017-10-11 Added net names
2017-10-15 Started board design
2017-10-18 Routed the board
2017-10-18 Fixed a trace
2017-10-18 Added datasheets
2017-10-19 Made traces the right size
2017-10-19 Prettied up the routing and added kill switch indicator
2017-10-19 fixed edge connector, no more dimension layer and power/ground planes fixed
2017-10-19 Lost all my work :( but at least I got the new edge connector
2017-10-20 added name to readme
2017-10-21 Applied changes suggested in design review
2017-10-21 Added testpoints
2017-10-21 Revised the 5V and 3.3V Converter files Created the 12V converter Began schematic for converter board Created block diagram
2017-10-22 Revising converter board
2017-10-22 Done, made gerbers, time for lunch
2017-10-22 Fixing backplane hole placement
2017-10-22 Added library for Depth Sensor Connector
2017-10-22 Revised 12 V and 3.3 V Converters Finished the majority of the converter board
2017-10-22 Added Sparkfun Library to eagle-libs
2017-10-22 Cleaning up the mess
2017-10-22 Got the gerber and also labeled the gnd test point
2017-10-23 Added LEDs and resistors to converter board
2017-10-24 Jennifer's edits on the converter board
2017-10-25 Renamed templates
2017-10-25 Fixing upstream
2017-10-25 added several eagle libraries, all "big" parts are on the copro schematic
2017-10-26 Attempted to make test points
2017-10-26 Made some final adjustments to the converter board
2017-10-26 Adjustments to the converter board
2017-10-27 Added battery gnd to backplane
2017-10-29 Adjustments to board, created gerber files
2017-11-05 some progress on the copro eagle schematic, optoisolator needs fixed
2017-11-05 Opto-isolator finished, usb port finished, jtag finished
2017-11-11 copro board schematic nearly finished. Still need to work out transceiver
2017-11-11 Slight progress on last commit, just so everything is up to date
2017-11-14 The current official coprocessor board is now saved under the filename "copro - copy". I will change that. More importantly, the board is tentatively finished, atleast enough for others to check it, 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
2017-11-14 renamed the current official copro board to filename "Coprocessor_Board"
2017-11-15 completely rerouted, about 3/4 routed. many resistors switched to through-hole. opto-isolators moved for more space. gnd planes reworked.
2017-11-16 Fixed 3.3V converter Added extra connector Updated board with new parts
2017-11-19 coprocessor board tentatively finished draft2, many things fixed, CAN kicked the can, and parts list added
2017-11-19 Created a copy of rev, created a humidity sensor library
2017-11-19 Started Rev2
2017-11-21 copro finished check for mistakes
2017-11-28 General clean (salute) up of copro
2017-11-28 Smash
2017-11-28 L A B E L S
2017-11-28 Clean up
2017-11-28 Fixing USB lines, we RF now boyz
2017-11-28 Trace clean up
2017-11-28 Future proofing
2017-11-30 Adding gerbers
2017-11-30 Revised humidity sensor Started current sensor
2017-12-07 Finished current sensor and started temperature libraries
2017-12-10 Revision 2 of the battery balancer
2017-12-17 Last commit of the old copro
2017-12-17 Cleanup of coprocessor folder
2017-12-17 Last commit of Battery balancer Rev 1
2017-12-17 Removal of the old folder
2017-12-17 Initial commit of pnuematicsBoard
2017-12-17 Touched up the battery balancer
2017-12-17 Fixed optoisolator values
2017-12-18 Preliminary schematic finished, missing 5 V converter. Basic board layout complete, exception of Qs.
2017-12-18 Added 12V-5V Con. Q needs attention. Layout changed to 1x6 rect.
2018-01-09 Finished up sensor libraries, started cleaning up board schematic to begin adding new sensors
2018-01-11 Additions to Rev2, added sensors to schematic
2018-01-11 Updated board and added block diagram
2018-01-17 Pneumatics update - something incorrect with EAGLE GND planes
2018-01-17 Acoustics folder. Hope it doesn't break.
2018-01-20 Added Blaine's acoustics .sch - pneu almost done except for orphan adjustment
2018-01-21 Most recent version of converter board
2018-01-21 Rev 2 of Coprocessor Board (No IMU) 1.fixed wires that were flipped. JTAG 5 fixed to pin 50. JTAG 7 fixed to pin 46 2.LEDs for power 3.CAN 4.LEDs for CAN 5.Swapped Through-Hole Resistors with more sp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
2018-01-21 Finished Pneumatics Board, if RS232 still exists in a day
2018-01-24 Pneumatics Board complete. Gerber files uploaded.
2018-01-25 Moved C10, changed GND place on logic side.
2018-01-25 Added 0 Ohm Resistors on TX and RX lines just in case.
2018-01-26 Crystal Circuit wasn't grounded
2018-01-28 replaced 5v can tran with correct 3.3v
2018-01-28 Computer might blow up
    Schematic done
2018-01-28 Added the other adcs on the acoustics board
2018-02-02 2 pin connector for can. please check... USB moved No usb id line Different switch connector, custom-made 12 pin package Esc names horizontal LEDs for programming Pushbutton for programming 4 leds , 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
2018-02-03 added gpio pin connector, erc, fixed some air wires
2018-02-03 fixed ground, added labels for gpio pins
2018-02-04 Finished it up and made the gerber files
2018-02-04 Added acoustics reference generator
2018-02-04 Update from Jennifer Feb 4th
2018-02-04 Added Board v0.2
    Other files like basic parts list and Micro-controller files.
2018-02-05 fixed led orientation, added switch to switch connector
2018-02-07 PN - changed VD to Reg, added pressure sensor, added silkscreen to proper layer
2018-02-07 remove rouge names from readme
2018-02-08 Changed regulator position, fixed traces
2018-02-09 Added 8 pin connector
2018-02-09 Widened minifit holes
2018-02-09 Adding the converter board gerbers
2018-02-09 Adding copro gerbers revision 2
2018-02-09 General cleanup (salutes) of the converter and copro eagle files
2018-02-09 Added water mark and fixed the .6 mm blunder
2018-02-09 Adding the gerbers, last working commit of batBalance Revision 2
2018-02-11 Rev 0.3
2018-02-11 Added THS VSSOP-8 package, added reference data sheets
2018-02-18 Ver. 0.4
    Buzzer, address pins, GP LEDs, labels
2018-02-19 Rev 1 done
    Gerber Zip created
2018-02-25 Cleaned up file structure and commit gerbers
2018-02-27 Added basic opa - package NEEDS changed. no values4passive components
2018-03-02 Will this commit?
2018-03-04 Acoustics Schematic Finished
2018-03-04 Added passive components around differencial amplifier. Yikes.
2018-03-04 Coprocessor 3.0 Schematic
2018-03-04 Updated lables position and content
2018-03-07 Mega cleanup and initial placement of rev3 parts
2018-03-08 Final-ish placement of parts
2018-03-08 (Hulk) Smash
2018-03-08 Adding labels to everything
2018-03-09 Fixed THS 4551 library and Acoustics Schematic
2018-03-09 Added Final Bulk Decoupling cap, updated lables, Gerber files are not updated to reflect new cap yet.
2018-03-09 Fix name placement of nanofit header
2018-03-09 Added low pass filter, ran DRC fixed weird issue
2018-03-18 Create BatteryMonitor
2018-03-18 Created Documentarion for Rev 1.0 Needs Picture of assembled board, and code documentation
2018-03-20 Merging to fix with the stuff
2018-03-20 Orginazed directory, generated documentation in Markdown
2018-04-01 Cleaned and updated converter board, added spots for capacitors
2018-04-01 Removed battery monitor files
2018-04-01 Add battery monitor eagle schematic and board
2018-04-05 One channel done-ish for 4/5 meeting with Dave
2018-04-06 One channel done updated Dave's suggestions
2018-04-09 Combining AGND and GND into one
2018-04-09 Debug Board. Should be done.
2018-04-09 Battery monitor board is updated with spi headers
2018-04-09 jk lol unmirrored everything
2018-04-10 Initial placement of parts completed
2018-04-10 Clean up for Jennifer
2018-04-11 Fixing connector placement of signal connectors
2018-04-11 Fixing channel 4 to match the others
2018-04-11 Fixing planes and matching bounding box
2018-04-11 open invitation for august to mess with this layout before he yells at me
2018-04-11 Adding power connection to acoustics
2018-04-12 Fixing the power connector to add spot for nub
2018-04-12 Added correct capacitors, rearranged parts
2018-04-13 Finished Rev 3 of converter board
2018-04-15 Finished rev3 of board, made gerber files
2018-04-25 Adding connectors and labels
2018-04-29 Revamped Converter Board
2018-05-15 Commit for cleanup
2018-05-15 Fixing acoustics branch up to date now
2018-05-18 Fixing schematic of new ADC package
2018-05-18 Proper ADC library for our package
2018-05-21 Finished routing ADC
2018-09-10 Gitignore and starting acoustics rev 2
2018-09-23 Labelled Acoustics input connectors.
2018-09-23 Changing Labels and fixing Layout of Acoustic board
2018-09-23 Changing Labels and fixing Layout of Acoustic board (#102)
2018-09-27 Added more connections
2018-09-27 Added more connections (#103)
2018-09-28 Finished PA channel
2018-09-28 Finished PA channel (#104)
